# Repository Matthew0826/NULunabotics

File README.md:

Welcome to the NU Lunabotics Repository! This is the place for all IP for NU Lunabotics.

For Github to commit changes correctly ensure you run:
$ git config --global core.fileMode false

To run the repository in a docker container:
1. Open the project from the ROS folder (important so it can recognize our Dockerfile)
2. Ctrl + Shift + P
3. Open and Rebuild Container
4. $ ./launch_theia.sh to run the website + theia

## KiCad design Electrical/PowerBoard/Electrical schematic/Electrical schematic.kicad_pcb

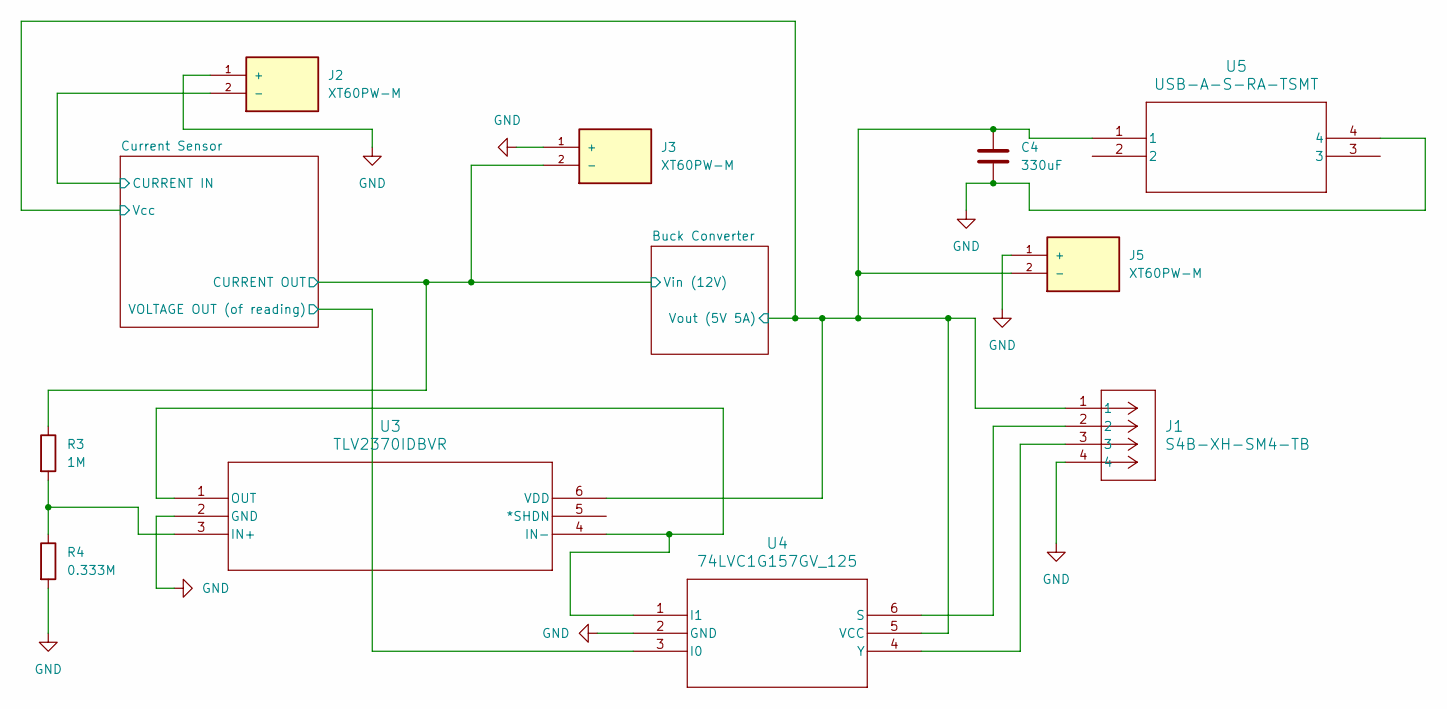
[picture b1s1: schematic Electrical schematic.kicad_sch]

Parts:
C4: 330uF; C_0805_2012Metric_Pad1.18x1.45mm_HandSolder
J1: S4B-XH-SM4-TB; JST_XH_B4B-XH-A_1x04_P2.50mm_Vertical
J2, J3, J5: XT60PW-M; AMASS_XT60IPW-M_1x03_P7.20mm_Horizontal; PARTREV V1.2
R3: 1M; R_0805_2012Metric_Pad1.20x1.40mm_HandSolder
R4: 0.333M; R_0805_2012Metric_Pad1.20x1.40mm_HandSolder
U3: TLV2370IDBVR; DBV6
U4: 74LVC1G157GV_125; TSOP6_SOT457_NEX
U5: USB-A-S-RA-TSMT; USB-A-S-RA-TSMT_ADM

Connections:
/Buck Converter/Vin (12V): J3.2 (-), R3.1; also elsewhere on the board
/Buck Converter/Vout (5V 5A): C4.2, J1.1, J5.2 (-), U3.6 (VDD), U4.5 (VCC), U5.1; also elsewhere on the board
/Current Sensor/CURRENT IN: J2.2 (-); also elsewhere on the board
/Current Sensor/VOLTAGE OUT (of reading): U4.3 (I0); also elsewhere on the board
GND: C4.1, J1.4, J2.1 (+), J3.1 (+), J5.1 (+), R4.2, U3.2 (GND), U4.2 (GND), U5.4; also elsewhere on the board
unnamed: R3.2, R4.1, U3.3 (IN+)
unnamed: U3.1 (OUT), U3.4 (IN-), U4.1 (I1)
unnamed: J1.2, U4.6 (S)
unnamed: J1.3, U4.4 (Y)

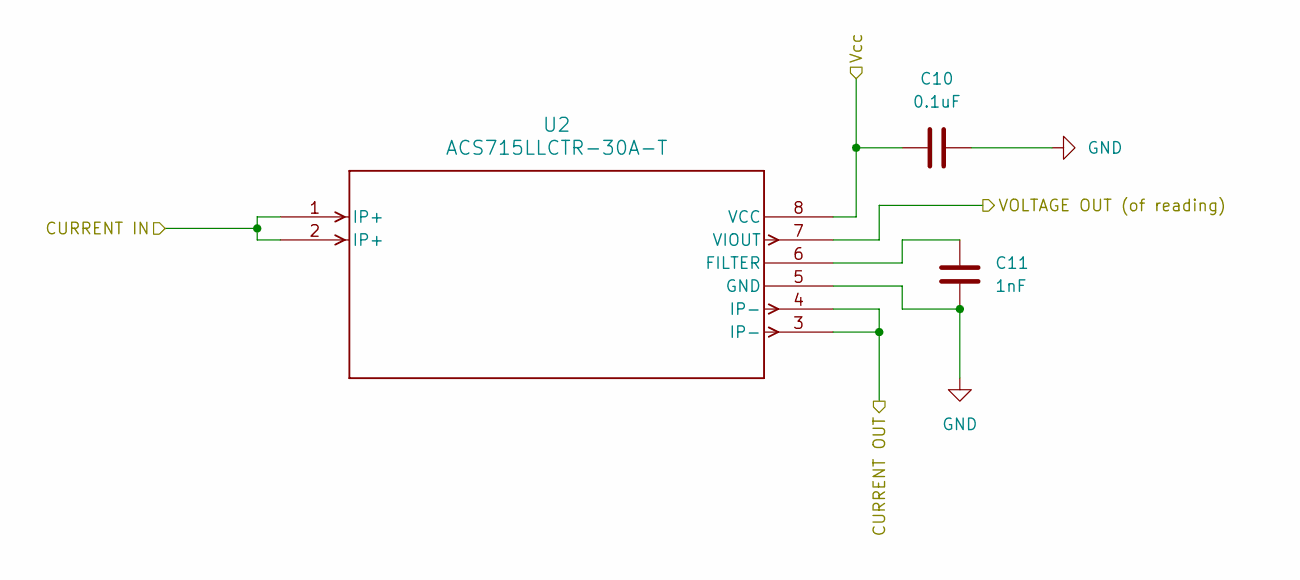
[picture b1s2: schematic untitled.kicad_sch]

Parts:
C10: 0.1uF; C_0805_2012Metric_Pad1.18x1.45mm_HandSolder
C11: 1nF; C_0805_2012Metric_Pad1.18x1.45mm_HandSolder
U2: ACS715LLCTR-30A-T; SOIC-8_ALM

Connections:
/Buck Converter/Vin (12V): U2.3 (IP-), U2.4 (IP-); also elsewhere on the board
/Buck Converter/Vout (5V 5A): C10.1, U2.8 (VCC); also elsewhere on the board
/Current Sensor/CURRENT IN: U2.1 (IP+), U2.2 (IP+); also elsewhere on the board
/Current Sensor/VOLTAGE OUT (of reading): U2.7 (VIOUT); also elsewhere on the board
GND: C10.2, C11.2, U2.5 (GND); also elsewhere on the board
unnamed: C11.1, U2.6 (FILTER)

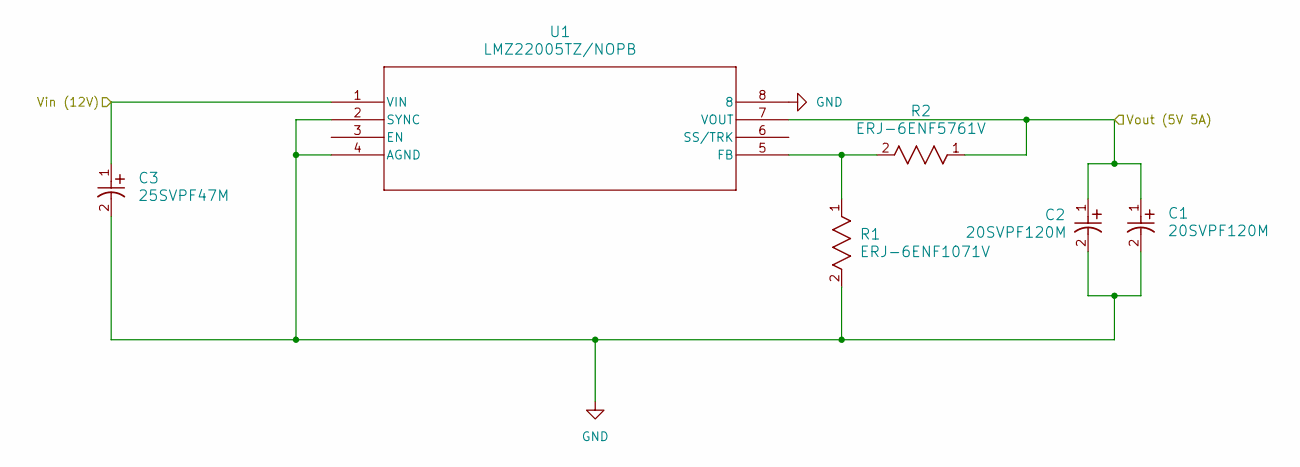
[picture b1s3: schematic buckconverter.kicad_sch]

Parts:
C1, C2: 20SVPF120M; PCAP_SVP_C6_PAN
C3: 25SVPF47M; PCAP_SVP_C6_PAN
R1: ERJ-6ENF1071V; RC0805N_PAN
R2: ERJ-6ENF5761V; RC0805N_PAN
U1: LMZ22005TZ/NOPB; TZA07A

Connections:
/Buck Converter/Vin (12V): C3.1, U1.1 (VIN); also elsewhere on the board
/Buck Converter/Vout (5V 5A): C1.1, C2.1, R2.1, U1.7 (VOUT); also elsewhere on the board
GND: C1.2, C2.2, C3.2, R1.2, U1.2 (SYNC), U1.4 (AGND), U1.8; also elsewhere on the board
unnamed: R1.1, R2.2, U1.5 (FB)

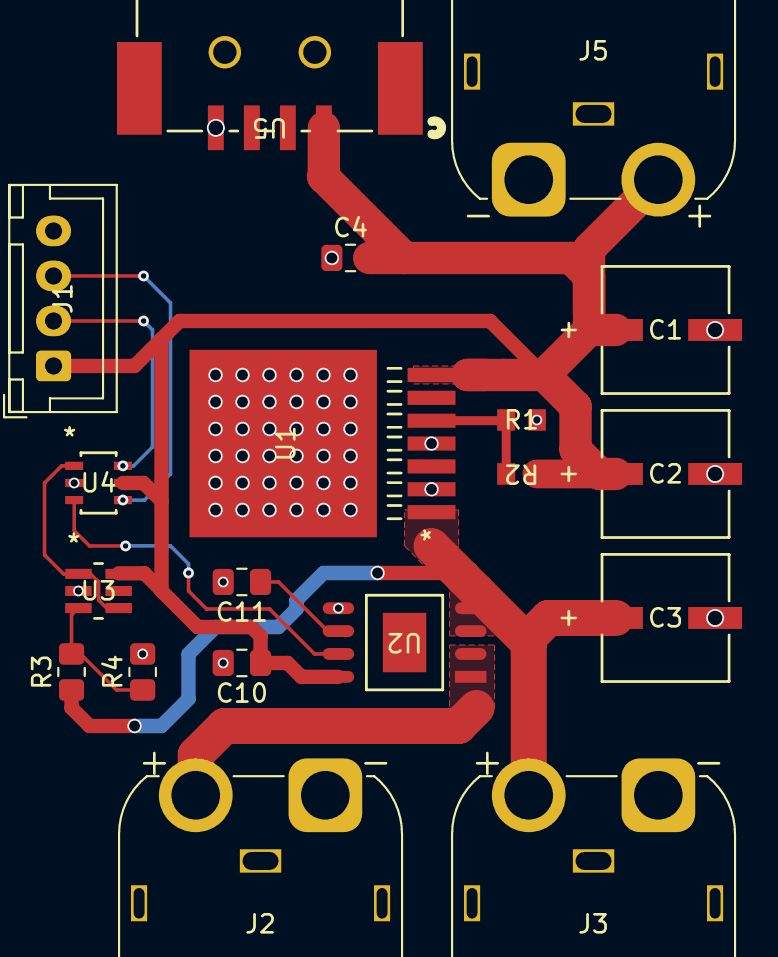
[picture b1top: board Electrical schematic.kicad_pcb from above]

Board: 2 copper layers, 19 parts (0 on the bottom side), 11 nets.

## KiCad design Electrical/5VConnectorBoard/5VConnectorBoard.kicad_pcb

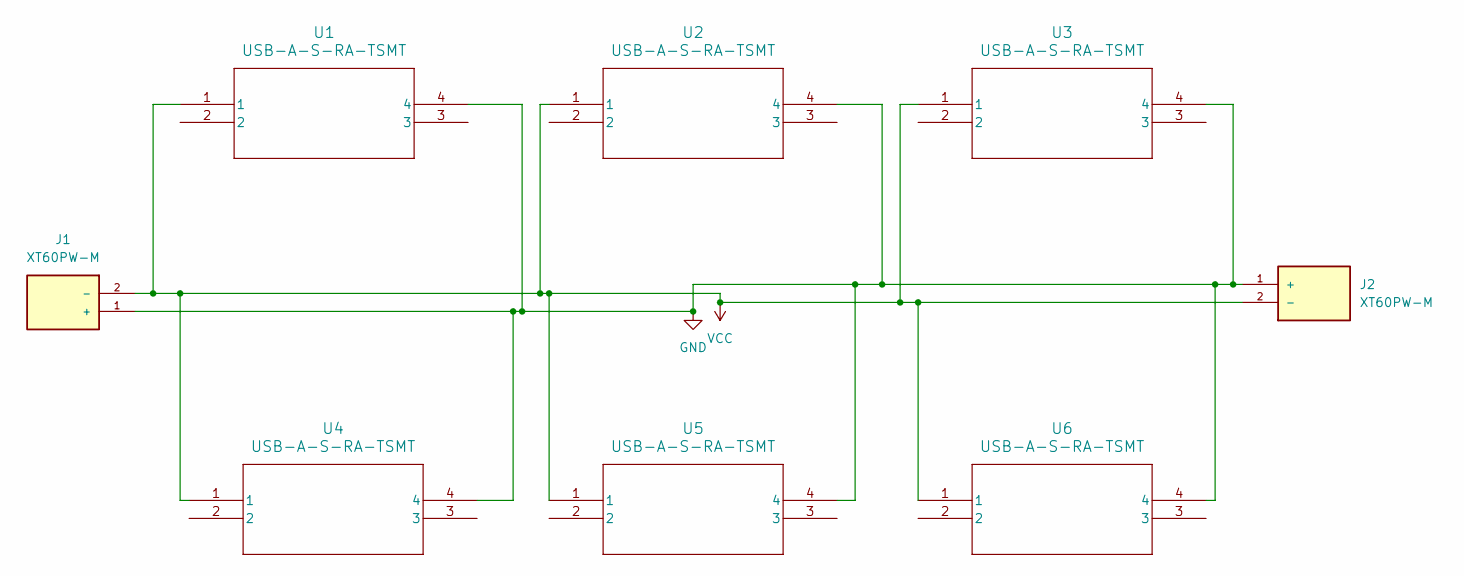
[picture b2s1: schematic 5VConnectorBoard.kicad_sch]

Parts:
J1, J2: XT60PW-M; AMASS_XT60PW-M_1x02_P7.20mm_Horizontal; PARTREV V1.2
U1, U2, U3, U4, U5, U6: USB-A-S-RA-TSMT; USB-A-S-RA-TSMT_ADM

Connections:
GND: J1.1 (+), J2.1 (+), U1.4, U2.4, U3.4, U4.4, U5.4, U6.4
VCC: J1.2 (-), J2.2 (-), U1.1, U2.1, U3.1, U4.1, U5.1, U6.1

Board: 2 copper layers, 8 parts (0 on the bottom side), 2 nets, no tracks yet.

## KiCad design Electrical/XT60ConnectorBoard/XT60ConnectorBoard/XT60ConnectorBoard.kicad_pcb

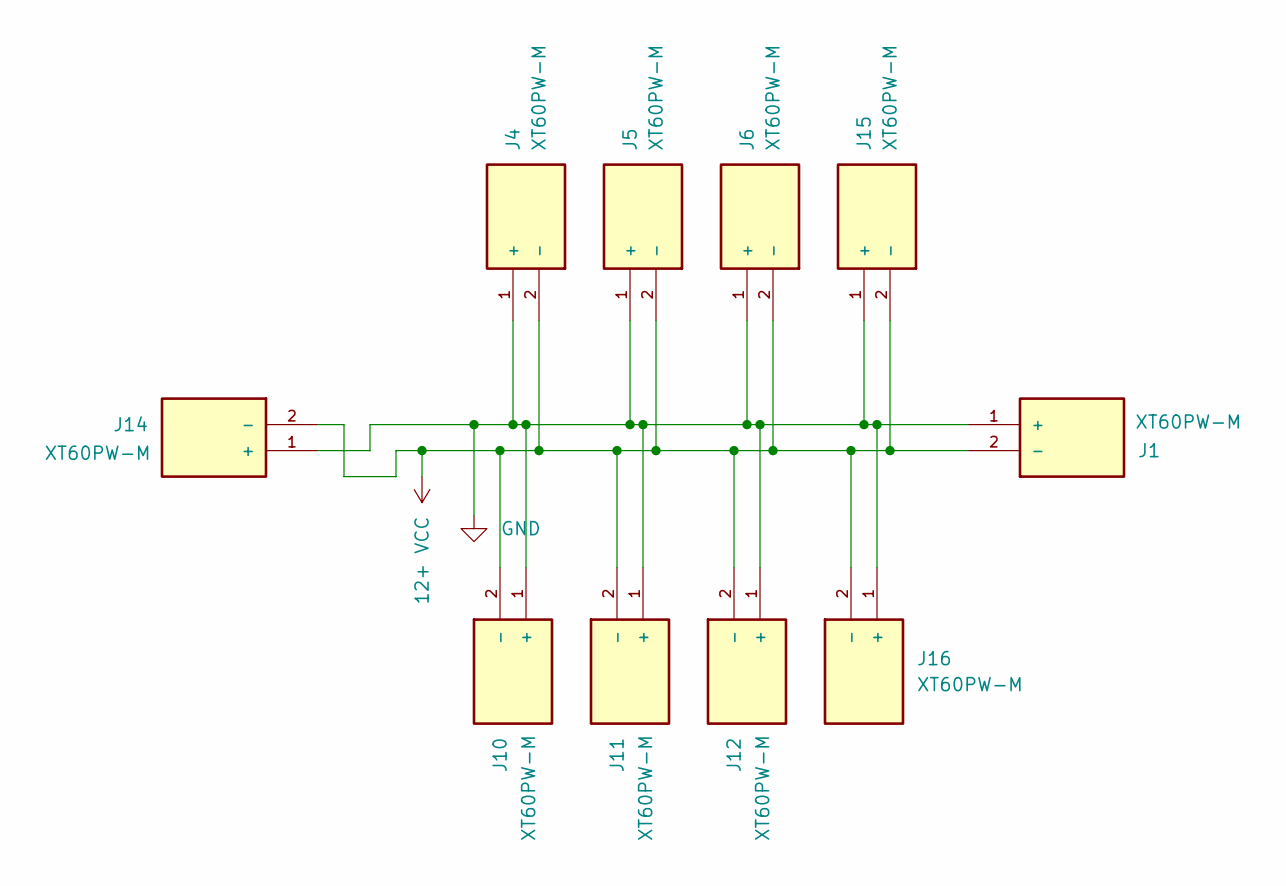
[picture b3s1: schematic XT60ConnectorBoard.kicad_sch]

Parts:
J1, J4, J5, J6, J10, J11, J12, J14, J15, J16: XT60PW-M; AMASS_XT60PW-M_1x02_P7.20mm_Horizontal; PARTREV V1.2

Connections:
12+ VCC: J1.2 (-), J4.2 (-), J5.2 (-), J6.2 (-), J10.2 (-), J11.2 (-), J12.2 (-), J14.2 (-), J15.2 (-), J16.2 (-)
GND: J1.1 (+), J4.1 (+), J5.1 (+), J6.1 (+), J10.1 (+), J11.1 (+), J12.1 (+), J14.1 (+), J15.1 (+), J16.1 (+)

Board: 2 copper layers, 10 parts (0 on the bottom side), 2 nets, no tracks yet.

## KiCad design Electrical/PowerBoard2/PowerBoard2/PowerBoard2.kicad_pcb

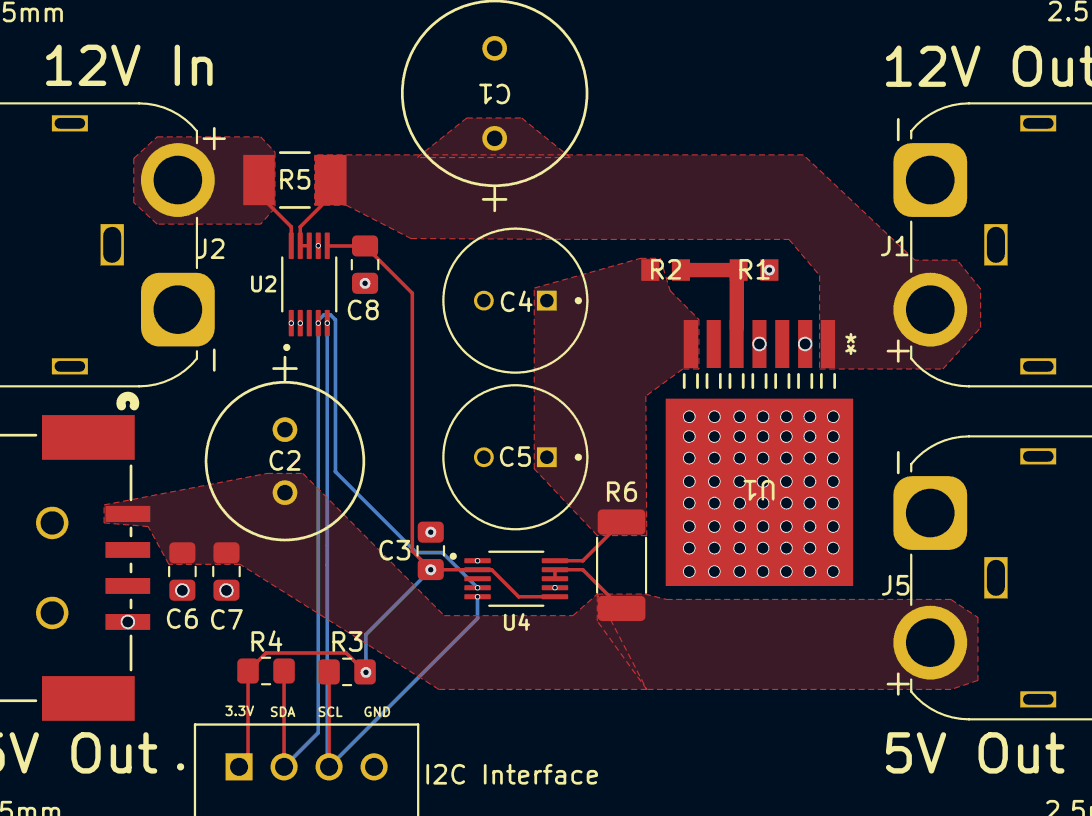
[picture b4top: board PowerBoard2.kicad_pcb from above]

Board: 2 copper layers, 26 parts (0 on the bottom side), 9 nets.

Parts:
2.5mm, 2.5mm#2, 2.5mm#3, 2.5mm#4: MountingHole_2.5mm
5V Out: USB-A-S-RA-TSMT; USB-A-S-RA-TSMT_ADM
C1: PLF1E470MDO2TD
C2: 16ZLJ470MTA8X11.5; CAP_YX_8X11P5_RUB
C3, C7, C8: 0.1uF; C_0805_2012Metric_Pad1.18x1.45mm_HandSolder
C4, C5: 25SEK120M
C6: 10uF; C_0805_2012Metric_Pad1.18x1.45mm_HandSolder
I2C Interface: B4B-XH-A_LF__SN_; JST_B4B-XH-A_LF__SN_
J1, J2, J5: XT60PW-M; AMASS_XT60IPW-M_1x03_P7.20mm_Horizontal
R1: ERJ-6ENF1071V; RC0805N_PAN
R2: ERJ-6ENF5761V; RC0805N_PAN
R3, R4: 10k; R_0805_2012Metric_Pad1.20x1.40mm_HandSolder
R5: CSNL2010FT2L00; STA_CSNL2010&lessthan_=3_STP
R6: CSNL2010FT2L00; R_2010_5025Metric_Pad1.40x2.65mm_HandSolder
U1: LMZ22005TZ/NOPB; TZA07A
U2, U4: INA226AIDGSR

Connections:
+3.3V: C3.1, C8.1, I2C Interface.1, R3.1, R4.1, U2.6 (VS), U4.2 (A0), U4.6 (VS)
+5V: 5V Out.1, C2.2, C6.1, C7.1, J5.2 (-), R6.1, U4.8 (VBUS), U4.9 (IN-)
+12V: C1.1, J1.2 (-), R5.2, U1.1 (VIN), U2.8 (VBUS), U2.9 (IN-)
/Buck Converter/Vout (5V 5A): C4.1, C5.1, R2.1, R6.2, U1.7 (VOUT), U4.10 (IN+)
/SCL: I2C Interface.3, R3.2, U2.5 (SCL), U4.5 (SCL)
/SDA: I2C Interface.2, R4.2, U2.4 (SDA), U4.4 (SDA)
GND: 5V Out.4, C1.2, C2.1, C3.2, C4.2, C5.2, C6.2, C7.2, C8.2, I2C Interface.4, J1.1 (+), J2.1 (+), J5.1 (+), R1.2, U1.2 (SYNC), U1.4 (AGND), U1.8, U2.1 (A1), U2.2 (A0), U2.7 (GND), U4.1 (A1), U4.7 (GND)
unnamed: J2.2 (-), R5.1, U2.10 (IN+)
unnamed: R1.1, R2.2, U1.5 (FB)

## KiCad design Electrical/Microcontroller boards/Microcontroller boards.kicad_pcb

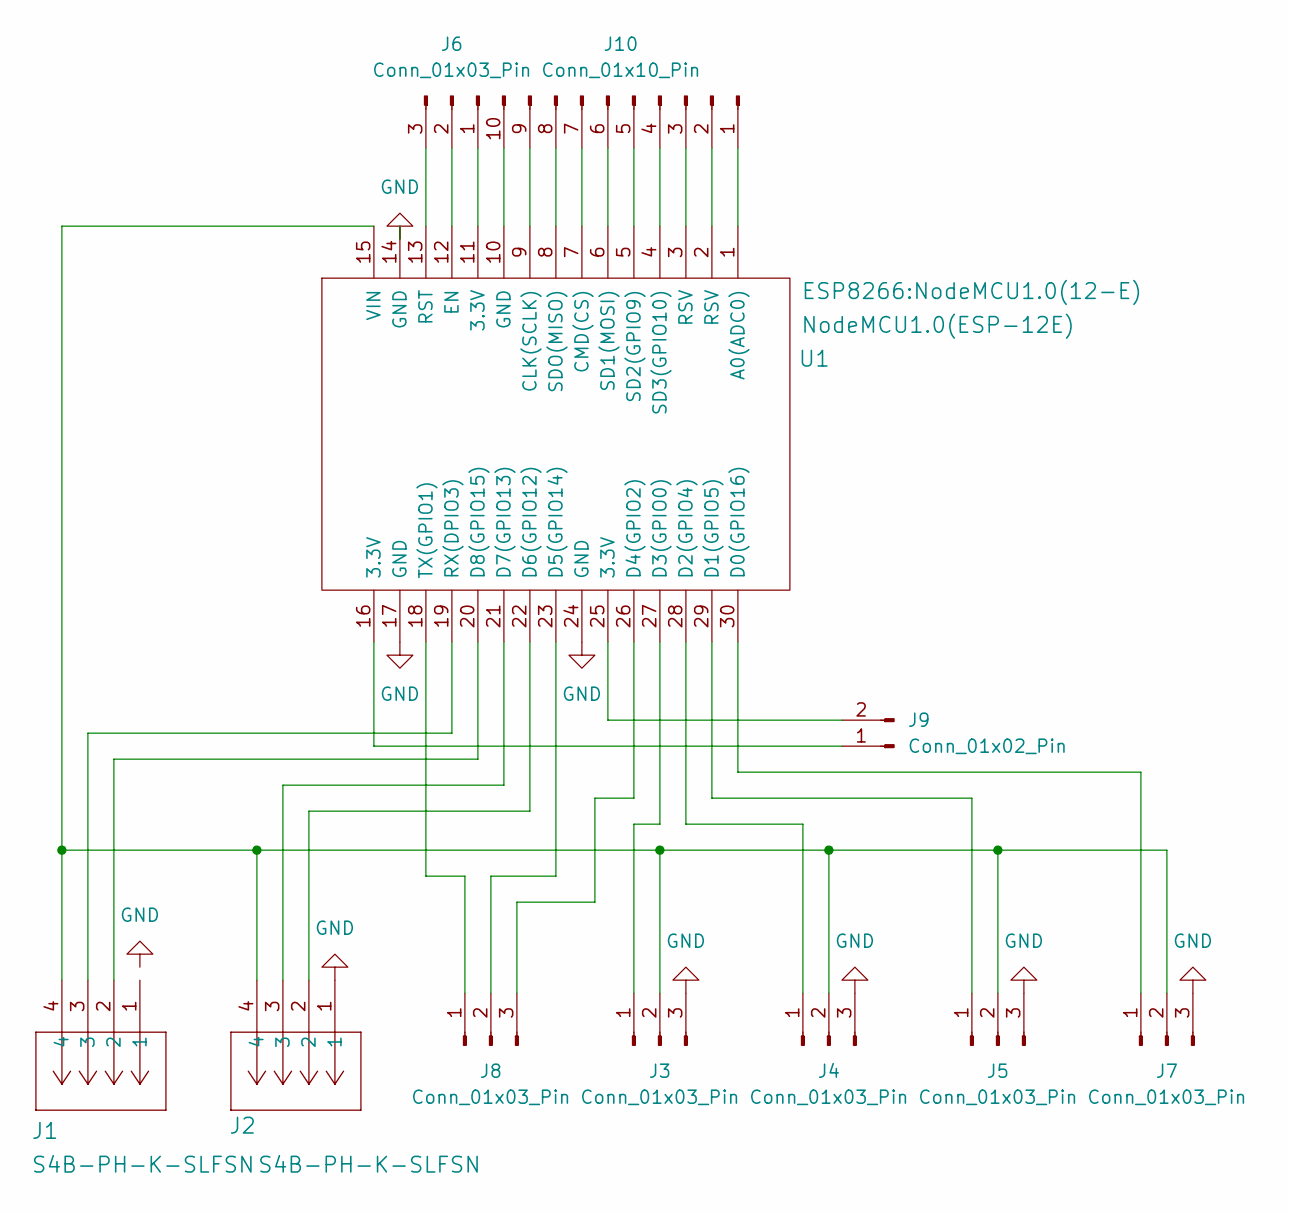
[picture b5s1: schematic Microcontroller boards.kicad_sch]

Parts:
J1, J2: S4B-PH-K-SLFSN; CONN_S4B-PH-K-S_JST
J3, J4, J5, J6, J7, J8: Conn_01x03_Pin; Wuerth_WR-WTB_64800311622_1x03_P1.50mm_Vertical
J9: Conn_01x02_Pin; Wuerth_WR-WTB_64800311622_1x02_P1.50mm_Vertical
J10: Conn_01x10_Pin; Wuerth_WR-WTB_64801011622_1x10_P1.50mm_Vertical
U1: NodeMCU1.0(ESP-12E); NodeMCU1.0(12-E)

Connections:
GND: J2.1, J3.3, J4.3, J5.3, J7.3, U1.14 (GND), U1.17 (GND), U1.24 (GND)
unnamed: J3.1, U1.27 (D3(GPIO0))
unnamed: J1.4, J2.4, J3.2, J4.2, J5.2, J7.2, U1.15 (VIN)
unnamed: J4.1, U1.28 (D2(GPIO4))
unnamed: J5.1, U1.29 (D1(GPIO5))
unnamed: J6.1, U1.11 (3.3V)
unnamed: J6.2, U1.12 (EN)
unnamed: J6.3, U1.13 (RST)
unnamed: J7.1, U1.30 (D0(GPIO16))
unnamed: J8.1, U1.18 (TX(GPIO1))
unnamed: J8.2, U1.23 (D5(GPIO14))
unnamed: J8.3, U1.26 (D4(GPIO2))
unnamed: J9.1, U1.16 (3.3V)
unnamed: J9.2, U1.25 (3.3V)
unnamed: J10.1, U1.1 (A0(ADC0))
unnamed: J10.2, U1.2 (RSV)
unnamed: J10.3, U1.3 (RSV)
unnamed: J10.4, U1.4 (SD3(GPIO10))
unnamed: J10.5, U1.5 (SD2(GPIO9))
unnamed: J10.6, U1.6 (SD1(MOSI))
unnamed: J10.7, U1.7 (CMD(CS))
unnamed: J10.8, U1.8 (SDO(MISO))
unnamed: J10.9, U1.9 (CLK(SCLK))
unnamed: J10.10, U1.10 (GND)
unnamed: J2.2, U1.22 (D6(GPIO12))
unnamed: J2.3, U1.21 (D7(GPIO13))
unnamed: J1.2, U1.20 (D8(GPIO15))
unnamed: J1.3, U1.19 (RX(DPIO3))

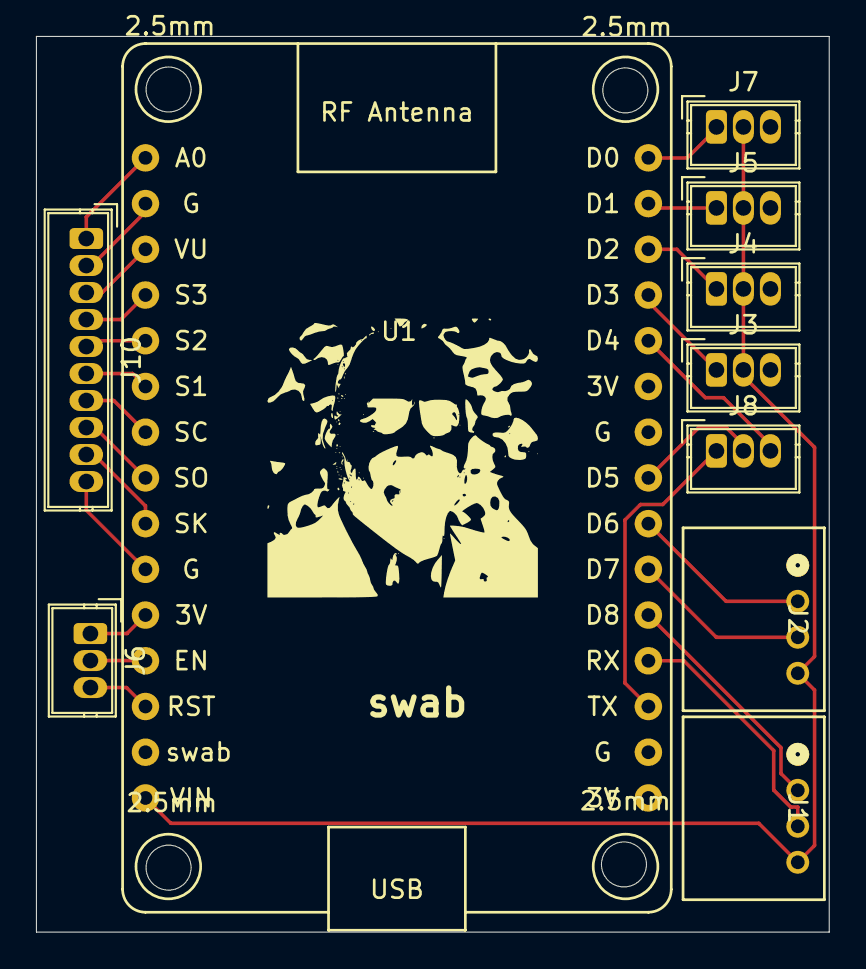
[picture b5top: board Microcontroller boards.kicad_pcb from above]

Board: 2 copper layers, 44.0 x 49.8 mm, 15 parts (0 on the bottom side), 26 nets.

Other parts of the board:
2.5mm, 2.5mm#2, 2.5mm#3, 2.5mm#4: MountingHole_2.5mm
swab: LOGO

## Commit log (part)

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2025-02-10 Temporarily removed prepare script from package.json
2025-02-10 Github actions doesn't like "SOCKET" in routes without the prepare script
2025-02-10 No more route.ts
2025-02-10 Fixed web sockets!!
2025-02-10 Added types/ws to maybe fix the build error?
2025-02-10 Sends gamepad data over web socket whenever it changes
2025-02-11 Resolved type error with chart config
2025-02-11 Dashes
2025-02-11 Update nextjs.yml with test
2025-02-11 Brought back older version of nextjs.yml
2025-02-11 Turns out you really need those paths, huh
2025-02-11 Tried zipping up build first
2025-02-11 Attempt at stealing the code from the start deployment and using sshpass
2025-02-11 Uncommented something important
2025-02-11 Made the it auto run the shell script
2025-02-11 Actually, nevermind
2025-02-14 Updated some packages
2025-02-16 Made some small changes to which packages we're using
2025-02-20 Changed File Structure
2025-02-21 Added blocking
2025-02-21 Added some LiDAR stuff
2025-02-21 Fixed issue with global.css import
2025-02-21 Downgrade nextjs to 15.1.6 to stop typing "y"
2025-02-22 Reverted change that reordered the pnpm install step in the github action
2025-02-22 Made the ssh command use a password to do sudo commands (this really needs a better solution at some point)
2025-02-22 Added back missing single quote
2025-02-22 Gave selene permission on /var/www/lunabotics and removed the sudo part
2025-02-22 Made systemctl run in a script
2025-02-22 Going back to using echo 'admin' because the script still requires a password input
2025-02-22 new mux/usbA
2025-02-22 rewiring to be smaller/new mux/ fixing xt60
2025-02-22 Edited silkscreen labels, moved USB port to edge
2025-02-22 Rerouted Some Things
2025-02-23 finishing pcb
    adding mounting holes and different resistor for buck converter to convert to 5.15V.
2025-02-23 adding horizontal surface mount usba
2025-02-23 silkscreen
2025-02-23 idk i did something
2025-02-23 something else?
2025-02-23 Made the workflow only run on changes to the nextjs folder
2025-02-23 Added quotes around the paths
2025-02-24 Added Dylan's wheel and also other things apparently
2025-02-24 More formatting work, and fixed the gamepad displays
2025-02-25 something idk
2025-02-25 Added obstacles, and more styling (finally map should fit on all displays and be correct aspect ratio)
2025-02-26 xt60board
2025-02-26 Add files via upload
    New Chassis made of 1x1", 1/16" bars and gussets.
2025-02-27 2x1 shaft sketches
    Added 2x1 shaft sketches and spacers and added left and right excavator side sketches
2025-02-27 Added basic ros2 support
2025-02-28 Timer and Battery for UI implemen ted
2025-02-28 Fixed gamepad sending to server and temporarily removed ros functionality
2025-03-02 Create Chassis 3 Design
2025-03-02 Create dump
2025-03-12 Added things
2025-03-12 Excavator Mastersketch
    new gussets
2025-03-14 gussets!
2025-03-14 Updates from meeting
2025-03-16 Changed map to align with Cosmic competition map
2025-03-18 The blocking was outdated. Whoops.
2025-03-18 Reorganized Chassis Folder
2025-03-20 Chassis Work
2025-03-20 Changed next config to work with rclnodejs
2025-03-21 Added information from individual data point readings in lidar packet data
2025-03-23 Added files needed for ros2 to work
2025-03-24 Added timestamp to controller data
2025-03-25 Added lidar support
2025-03-25 Fixed issue with partial lidar data showing up on website
2025-03-25 Updated to new way of sending data points (all on one line)
2025-03-27 Switched back to 16 bit integers
2025-03-27 Add files via upload
    This drives one motor controller, receving a float from -1.0 to 1.0 via serial.
2025-03-28 3/27 Push from Dylan Kim
    3/27 Push from Dylan Kim
2025-03-28 3.27
2025-03-28 final version
2025-03-28 microcontroller
2025-03-28 Fixed Project Errors
2025-03-30 Moved web socket tracker to its own file
2025-03-30 Add lidar icon
2025-03-31 new size spacer
2025-03-31 new 2.22 excavator spacer
2025-03-31 Switched to using arduino nano and using the Servo library
2025-03-31 Made LiDAR moving average based on angle, not index in array
2025-04-01 Fixed issue with newest version of next-ws by reverting to version 2.0.0
2025-04-01 Got rid of unneeded nextjs build steps
2025-04-01 Trying to visualize how far points are from moving average
2025-04-02 Updated UWB code to work on new boards, and added accelerometer code to the tag file
2025-04-03 Added serial port identification with a ros2 service
2025-04-04 Added entire ros2 workspace, and moved nextjs project into that workspace
2025-04-04 Moved ros packages to src folder, and created interfaces for various types we are going to use
2025-04-04 Updated fields in interface msgs and added them as dependencies
2025-04-04 Switched to new msgs types for ros on website
2025-04-04 Added temp setup scripts
2025-04-06 Solved issue with serial port not finding response
2025-04-07 Added navigation package for autonomous
2025-04-07 Worked on detecting rocks and craters and published them to navigation/obstacles
2025-04-07 Added pathfinder service using astar pathfinding
2025-04-07 Create odometry.py
    Added odometry
2025-04-07 added face orientation
2025-04-07 ok not java anymore :(
2025-04-08 Added pathfinding
2025-04-08 Copied some changes over from the pi to improve run script
2025-04-08 Renamed files, moved astar into a file instead of a pip package, fixed run_ros script
2025-04-08 Added starter obstacles into website by default (these are ones we know will be there at the competition)
2025-04-09 Began working on planner to do autonomous driving
2025-04-09 nothing
2025-04-11 updated to start testing library
2025-04-11 added publish of orientation
2025-04-12 Added mock odometry which simulates controlling the robot, and worked on planner
2025-04-12 Prevented deadlock in the planner by using multi threaded executor
2025-04-12 Worked on incorporating planner into website
2025-04-13 Added mock obstacle detector, but it doesn't really work. and you can now click to add mock obstacles on the website
2025-04-13 Fixed mock obstacle detector!!
2025-04-13 Added some documentation to the rest of the navigation nodes, as well as splitting up functionality into their own helper files.
2025-04-13 Made it so robot has to discover all obstacles for itself
2025-04-15 mock
2025-04-16 Adding lots of stuff
2025-04-17 Updated Kalman filter and triangulation code to work with test setup and to work with ROS positioning node
2025-04-18 Add 2 new ekf files
    These aren't tested. Option 1 is supposed to take the linear x and y as control inputs in the prediction phase (I think it assumes they are low noise measurements) to directly predict the next veloci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
2025-04-18 finished
2025-04-18 Adding Vias
2025-04-19 Added power data board, fixed bugs with beacon code
2025-04-19 Added power data publisher and changed some consts for positioning
2025-04-19 finished xt60 board
2025-04-19 5Vconnectorboard
2025-04-20 Improved the stop predicate algorithm, but lots more needs to be done because sometimes it doesn't stop turning at the right time
2025-04-21 Added berm zone to map and backup of netplan file
2025-04-22 Power Board 2
2025-04-22 Added lidar fowarder, which takes packets from the ldlidar_stl_ros2 package provided by the lidar
2025-04-23 Got power data to correctly output current by dividing by 16 and switching pins around
2025-05-01 Added serial port manager for theia serial
2025-05-01 minor improvements
2025-05-02 Removed more uneeded files and updated setup.py files
2025-05-03 Added distance check to odometry
2025-05-03 okay new predicate
2025-05-03 Added stuff back from before in odo
2025-05-04 based on distance
2025-05-04 Odometry works guys! I promise
2025-05-04 added excavator power
2025-05-04 removed excavate motors from motors and added excavate msg type
2025-05-05 Moved positioning over to TheiaSerial and added more support for it with many different messages
2025-05-05 Made serial ports close gracefully when they are disconnected
2025-05-06 powerboard design
2025-05-07 PowerBoard 2 first iteration
2025-05-07 Updated Schematic, Rerouted Some Things
2025-05-07 Silkscreen Adjustments
2025-05-07 Added PID control to the simulation, and made it more realistic
2025-05-07 remove via
2025-05-07 widened traces for 5V output
2025-05-07 bypass capacitor
2025-05-07 shunt
2025-05-07 capacitors and opamps
2025-05-08 final alignment
2025-05-08 tweaked a bunch of parameters, added better visualizations and testing tools
2025-05-08 pads
2025-05-09 Updated Silkscreen
2025-05-09 Added PowerData.ino s.t. it works
2025-05-10 Added motors arduino code and fixed theiaserial
2025-05-11 Got positioning system going super speed (all theia serial stuff updates faster now!)
2025-05-11 Fixed bug with uwb tag by converting to degrees
2025-05-12 Removed unused files and greatly improved kalman filter
2025-05-12 Visualized uncertainty in robot position and added boundary check to kalman filter
2025-05-12 Added doc strings to the Kalman filter code
2025-05-12 cleaned up some code in motor driver; added exacavator driver; added support for going to positions backwards in odometry
2025-05-12 okay excavator progresso
2025-05-12 Added new obstacle detection system based on curvature instead of bumps
2025-05-12 latest with powers of excavator
2025-05-12 Switched to simpler feature detector and added tester to see if obstacle detection is working
2025-05-13 Switched to supporting 2 actuators for the excavator
2025-05-13 Added support for cancelling autonomous
2025-05-13 should unload in planner
2025-05-13 Added test
2025-05-13 Added changes from pi and got actuator working
2025-05-13 docker support
2025-05-14 fixed reverse driving
2025-05-14 Added 3d robot rendering (new 3d model coming soon)
2025-05-14 Fixed excavation simulation
2025-05-14 Move zone and pathfinding into its own folder and got zone visualization working
2025-05-14 connector board
2025-05-14 DistanceSensorCode
2025-05-15 Added orientation correction to find initial rotation
2025-05-15 Removed some debug messages and got orientation correction simulation working
2025-05-15 added right click to create mock obstacles
2025-05-16 Got obstacle detection working and switched to new method of controlling the excavator
2025-05-16 Potentially fixed delays on waiting for new messages to come into theia serial
2025-05-16 Typo
2025-05-16 Added toggle to panels on website, added i2c code for power data
2025-05-17 Got excavator teleop working
2025-05-18 setup script
2025-05-19 Added battery voltage
2025-05-19 Fixed auto scrolling problem on graph
2025-05-19 Got theia serial going fast
2025-05-20 Updated ThreeJS rendering of robot.
2025-05-20 Wheels spin different directions
2025-05-20 Added message listener for robot wheel speeds and context to handle it.
2025-05-20 Fixed a couple of issues with config
2025-05-21 Added lidar rendering to ThreeJS dashboard section
2025-05-21 Attempted to fix issues with auto tune
2025-05-21 A lot.
2025-05-21 Corrected lidar rendering in ThreeJS canvas.
2025-05-21 Updated lidar to display all points it's scanned at their global position.
2025-05-21 Corrected import.
2025-05-21 Major refactoring and type changes and assignment.
2025-05-21 Got tuner working and solved a few issues with new messages system on website
2025-05-22 Fixed slight type errors.
2025-05-22 Fixed robot view in 3d
2025-05-22 added textbox to motor power slider, welcome electrical
2025-05-22 Fixed robot group not being added to scene
2025-05-22 Added ground terrain mesh to render robot which reflects obstacles in the mesh.
2025-05-22 better slider
2025-05-22 merge2
2025-05-22 Fixed website hydration
2025-05-22 Added throttle to controls message to server.
2025-05-22 Made basic CAD for rockers
2025-05-22 moving files around
    moved bearing holder mirrored
2025-05-22 Updated the robot rendering to move terrain based on robot position and corrected lidar positioning.
2025-05-22 Updated dashboard UI
2025-05-23 updated lidar and lots of other things like tuning pid
2025-05-23 tuned the robot
2025-05-23 fixed sim
2025-05-23 Fixed excavator rendering
2025-05-24 more little tweaks i forgot about
